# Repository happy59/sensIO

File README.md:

# SensIO
Here's my upgrade for the Philips Senso. *It should work for any other coffee machine that use push buttons likewise*.
The upgrade is easily reversible. Feel free to take and upgrade this project !
3D print files are available at  [INSERT PRINTABLES LINK](lol%20prout).

I based this project out of a D1miniPro but it can be made with a classic NodeMCU or another ESP board with similar component *(be carefull the D1Mini, even if it has a 5v output, runs on 3,3v)*
## How it works

Using this interface you can :
 - Know if there's a cup
 - Stirr your cup
 - Turn on and off your senseo
 - brew a little or a large cup
 - know the coffee temperature
 - setup a timer for your coffee to be made

## What you need

 - Wemos D1miniPro
 - Few cables
 - 4 relay modules (3v coil)
 - 4 SOT23 A09T MOSFETs
 - 4 diodes
 - Few resistors
	 - 4x100K
	 - 4x1K
	 - 2x10K
 - DIY PCB
	 - If you can't engrave it yourself I suggest you to use a classic breadboard, replacing SOT23 with long legs mosfets
 - 5v source to power the D1mini
	 - I use an old phone charger
 - DC Motor (5V)
 - DS1820 waterproof temperature sensor
 - Sharp IR distance sensor
	 - It's absolutly overkill, any 1/0 laser braking sensor should work
 - 3D printed parts
 - 4 neodymium magnets
 - Few M3 screws
 - Rubber band
## How to do it
Prepare your PCB by soldering all the parts.
This PCB takes place in the spilled coffee tank, you have to drill some holes in it to wire the three buttons. **Don't forget to flash arduino code**, arduino will still be accessible but you'll have to re-open the machine's back to flash it.

Now you can solder wires to the buttons, these welds are pretty easy to do but **be carefull to unplug the machine** the big shiny plate is full of painfull high voltage (trust me, it is). Don't forget the motor cables (not like me), drill through the printed plate.

don't forget thermometer and IR sensor cables, take them to the back. Now you can close the bottom of the machine. Drill a hole for the thermometer and a window to screw the cup sensor. 
I made Y connections from 220v. One branch to the machine and the other to the phone charger. We'll put the phone charger right behind the watertank (safety first 🥴). I wrapped it in thermal sheath to isolate it.

You can put back all the part in place and look at the 3D printed parts.
Put the magnets in their housing. Add a rubber band and tight the magnet pulley in place with M3 screws. And glue the motor with his pulley in place.

Now you'll need to find the machine's IP. You can scan your wifi network with ugly windows commands. I suggest you tu use your rooter interface to find it.
Once you found it *(something like 192.168.X.XX)*, paste the ip in your browser and create a shortcut to it on your phone's desktop. You'll have access to the interface. Et voilà !

I suggest you to create a static IP for your machine. Otherwise, ip can change at each reboot of the rooter. You also can create an aliases for this ip. For exemple when you type "sensIO/" in the browser it'll redirect it to the ip.

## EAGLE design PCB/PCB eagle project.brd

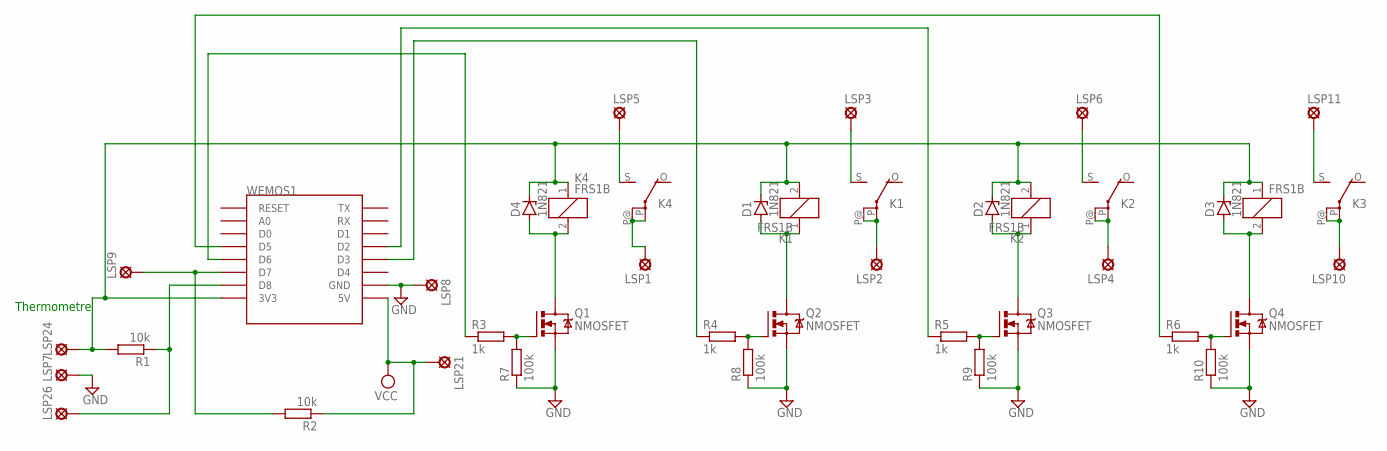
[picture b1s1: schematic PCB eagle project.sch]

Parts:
D1, D2, D3, D4: 1N821; DO35Z10
K1, K2, K3, K4: FRS1B
LSP1, LSP2, LSP3, LSP4, LSP5, LSP6, LSP7, LSP8, LSP9, LSP10, LSP11, LSP21, LSP24, LSP26: MCS10B
Q1, Q2, Q3, Q4: NMOSFET; SOT23
R1, R2: 10k; 0207/10
R3, R4, R5, R6: 1k; 0207/10
R7, R8, R9, R10: 100k; 0207/10
WEMOS1: ui; WEMOS-D1-MINI

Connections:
GND: LSP7.MP, LSP8.MP, Q1.2 (S), Q2.2 (S), Q3.2 (S), Q4.2 (S), R7.1, R8.1, R9.1, R10.1, WEMOS1.GND
unnamed: K4.S, LSP5.MP
unnamed: K3.S, LSP11.MP
unnamed: K1.S, LSP3.MP
unnamed: K4.P, K4.P@, LSP1.MP
unnamed: K1.P, K1.P@, LSP2.MP
unnamed: LSP26.MP, R1.1, WEMOS1.D8
unnamed: K2.S, LSP6.MP
unnamed: LSP9.MP, R2.2, WEMOS1.D7
unnamed: K2.P, K2.P@, LSP4.MP
unnamed: K3.P, K3.P@, LSP10.MP
unnamed: D1.C, D2.C, D3.C, D4.C, K1.2, K2.2, K3.1, K4.1, LSP24.MP, R1.2, WEMOS1.3V3
unnamed: D4.A, K4.2, Q1.3 (D)
unnamed: D1.A, K1.1, Q2.3 (D)
unnamed: D2.A, K2.1, Q3.3 (D)
unnamed: D3.A, K3.2, Q4.3 (D)
unnamed: Q1.1 (G), R3.2, R7.2
unnamed: Q2.1 (G), R4.2, R8.2
unnamed: Q3.1 (G), R5.2, R9.2
unnamed: Q4.1 (G), R6.2, R10.2
unnamed: R3.1, WEMOS1.D6
unnamed: R4.1, WEMOS1.D3
unnamed: R5.1, WEMOS1.D2
unnamed: R6.1, WEMOS1.D5
VCC: LSP21.MP, R2.1, WEMOS1.5V

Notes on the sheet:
Thermometre

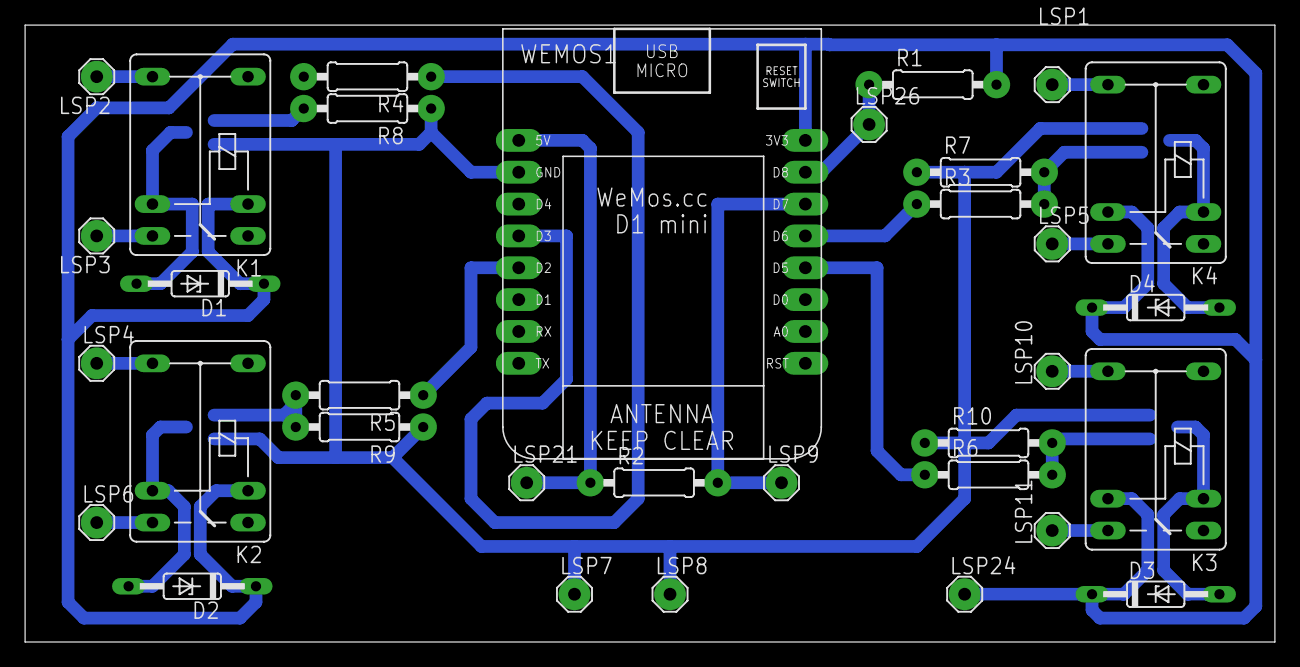
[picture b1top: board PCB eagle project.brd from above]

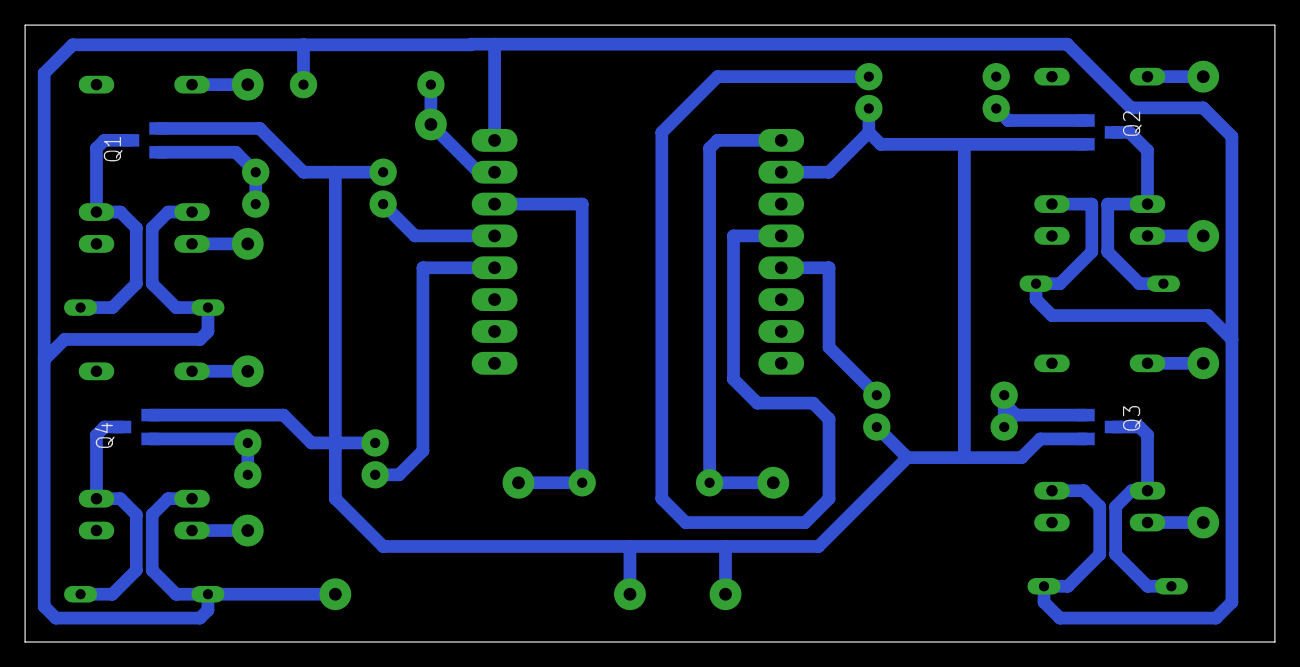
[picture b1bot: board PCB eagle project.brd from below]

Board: 2 copper layers, 99.7 x 49.2 mm, 37 parts (4 on the bottom side), 25 nets.

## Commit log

2023-01-15 Adding arduino files for the D1MiniPro
2023-01-15 Putting .ino file in a folder. Added CAM files for PCB Added screenshot of SensIO UI
